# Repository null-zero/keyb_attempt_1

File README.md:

# keyb_attempt_1
 trying to design a keyboard pcb

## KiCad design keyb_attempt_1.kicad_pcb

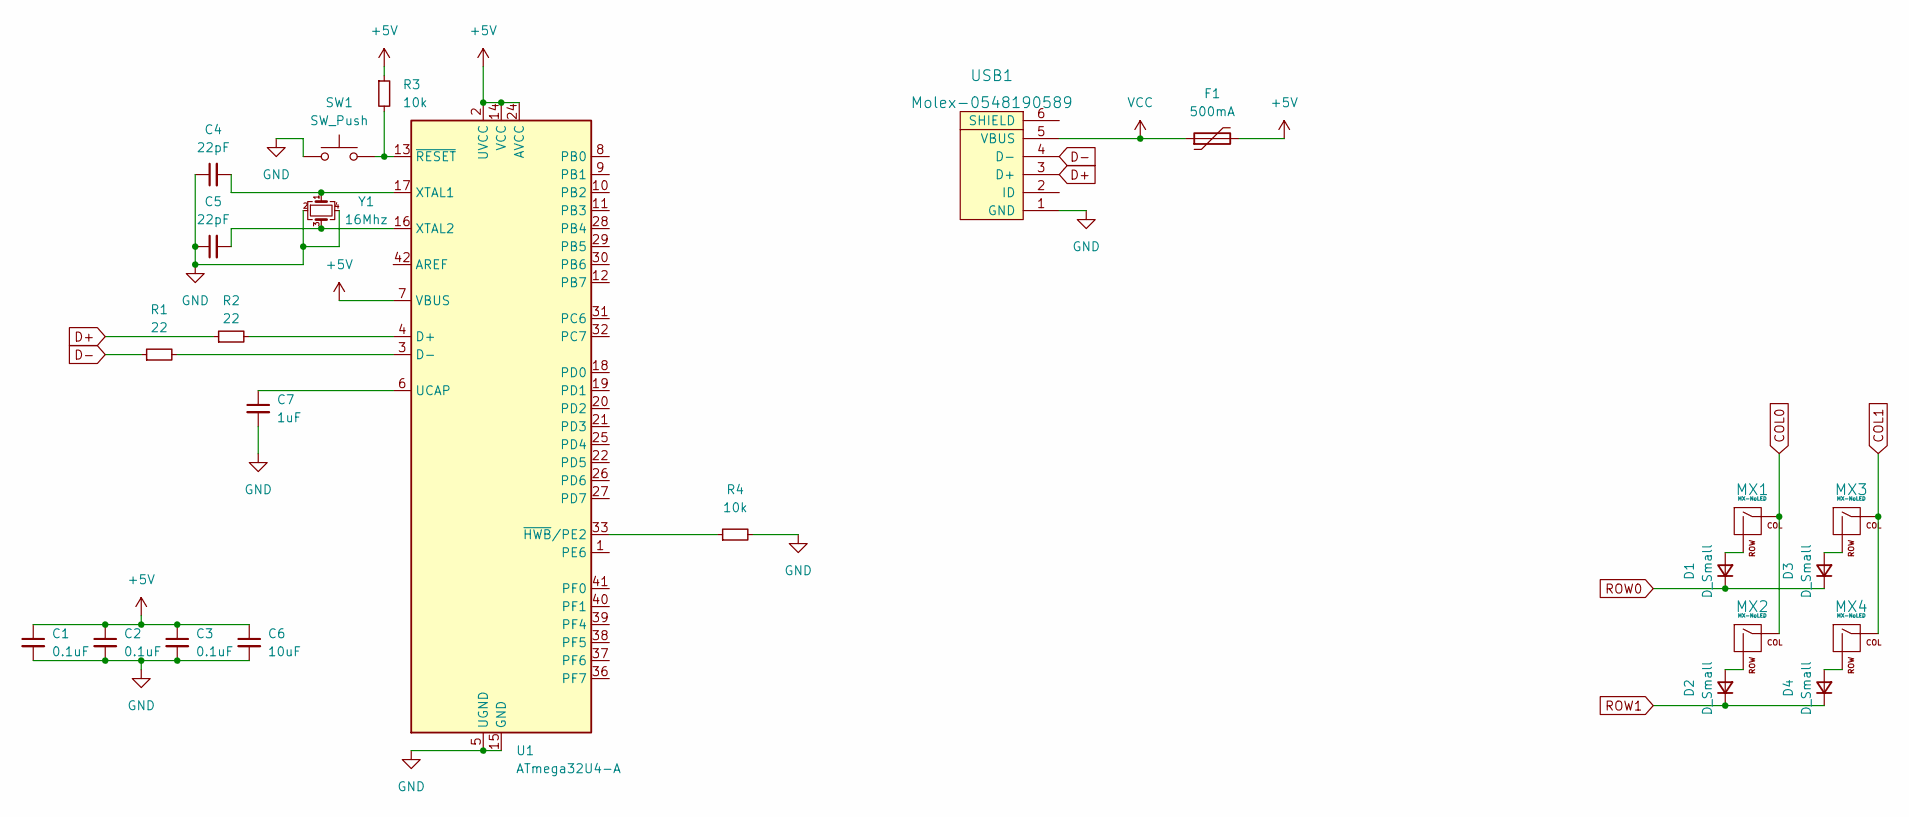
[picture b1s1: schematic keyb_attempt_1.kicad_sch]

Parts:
C1, C2, C3: 0.1uF; C_0805_2012Metric
C4, C5: 22pF; C_0805_2012Metric
C6: 10uF; C_0805_2012Metric
C7: 1uF; C_0805_2012Metric
D1, D2, D3, D4: D_Small; D_SOD-123
F1: 500mA; Fuse_1206_3216Metric
MX1, MX2, MX3, MX4: MX-NoLED; MX-1U-NoLED
R1, R2: 22; R_0805_2012Metric
R3, R4: 10k; R_0805_2012Metric
SW1: SW_Push; SKQG-1155865
U1: ATmega32U4-A; TQFP-44_10x10mm_P0.8mm
USB1: Molex-0548190589
Y1: 16Mhz; Crystal_SMD_3225-4Pin_3.2x2.5mm

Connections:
+5V: C1.1, C2.1, C3.1, C6.1, F1.2, R3.1, U1.2 (UVCC), U1.7 (VBUS), U1.14 (VCC), U1.24 (AVCC), U1.34 (VCC), U1.44 (AVCC)
COL0: MX1.1 (COL), MX2.1 (COL)
COL1: MX3.1 (COL), MX4.1 (COL)
D+: R2.1, USB1.3 (D+)
D-: R1.1, USB1.4 (D-)
GND: C1.2, C2.2, C3.2, C4.1, C5.1, C6.2, C7.2, R4.2, SW1.1, U1.5 (UGND), U1.15 (GND), U1.23 (GND), U1.35 (GND), U1.43 (GND), USB1.1 (GND), Y1.2, Y1.4
unnamed: C4.2, U1.17 (XTAL1), Y1.1
unnamed: C5.2, U1.16 (XTAL2), Y1.3
unnamed: C7.1, U1.6 (UCAP)
unnamed: D1.2 (A), MX1.2 (ROW)
unnamed: D2.2 (A), MX2.2 (ROW)
unnamed: D3.2 (A), MX3.2 (ROW)
unnamed: D4.2 (A), MX4.2 (ROW)
unnamed: R1.2, U1.3 (D-)
unnamed: R2.2, U1.4 (D+)
unnamed: R3.2, SW1.2, U1.13 (~RESET)
unnamed: R4.1, U1.33 (~HWB/PE2)
ROW0: D1.1 (K), D3.1 (K)
ROW1: D2.1 (K), D4.1 (K)
VCC: F1.1, USB1.5 (VBUS)

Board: 2 copper layers, 24 parts (16 on the bottom side), 20 nets, no tracks yet.

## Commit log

2022-05-20 init
2022-05-20 Add submodules
2022-05-20 Add footprint libraries
2022-05-20 MCU SCHEMATIC
